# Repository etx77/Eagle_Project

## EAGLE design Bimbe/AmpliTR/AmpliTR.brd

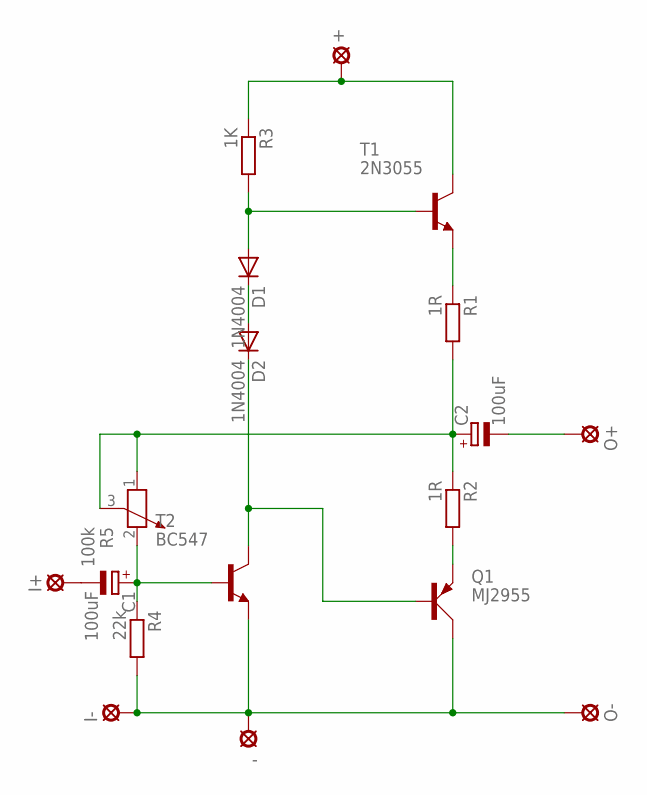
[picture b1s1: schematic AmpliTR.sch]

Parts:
+: LSP10
-: LSP10
C1, C2: 100uF; E2-5
D1, D2: 1N4004; DO41-10
I+: LSP10
I-: LSP10
O+: LSP10
O-: LSP10
Q1: MJ2955; TO3A
R1, R2: 1R; 0414V
R3: 1K; 0414V
R4: 22k; 0414V
R5: 100k; PT-10S
T1: 2N3055; TO3
T2: BC547; TO92

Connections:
unnamed: D1.C, D2.A
unnamed: D1.A, R3.2, T1.B
unnamed: +.MP, R3.1, T1.C, T1.C/ (C)
unnamed: R1.1, T1.E
unnamed: C2.+, R1.2, R2.1, R5.1, R5.3
unnamed: Q1.E, R2.2
unnamed: -.MP, I-.MP, O-.MP, Q1.C, Q1.C1 (C), R4.2, T2.1 (E)
unnamed: C1.+, R4.1, R5.2, T2.2 (B)
unnamed: D2.C, Q1.B, T2.3 (C)
unnamed: C2.-, O+.MP
unnamed: C1.-, I+.MP

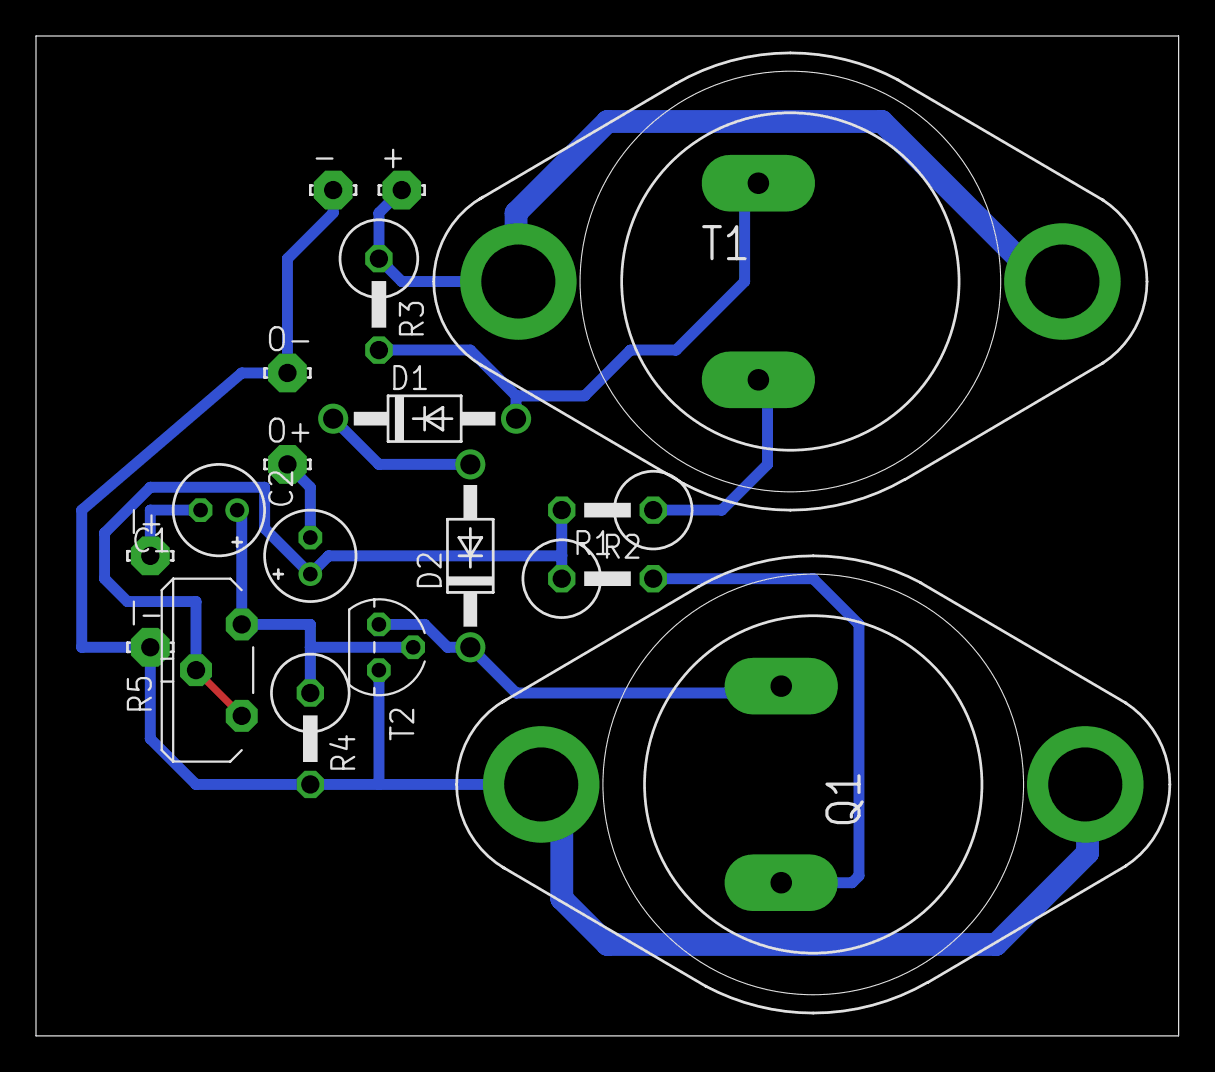
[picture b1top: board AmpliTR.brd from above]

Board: 2 copper layers, 63.5 x 55.5 mm, 18 parts (0 on the bottom side), 11 nets.

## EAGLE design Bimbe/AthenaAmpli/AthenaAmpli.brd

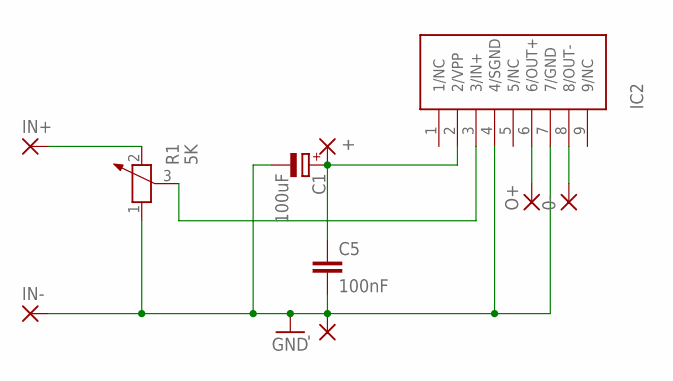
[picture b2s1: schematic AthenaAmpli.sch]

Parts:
0-: WIREPAD3,17/1,2; 3,17/1,2
+: WIREPAD3,17/1,2; 3,17/1,2
-: WIREPAD3,17/1,2; 3,17/1,2
C1: 100uF; E3,5-8
C5: 100nF; C050-024X044
IC2: TDA7056; SOT110-1
IN+: WIREPAD3,17/1,2; 3,17/1,2
IN-: WIREPAD3,17/1,2; 3,17/1,2
O+: WIREPAD3,17/1,2; 3,17/1,2
R1: 5K; PT-10S

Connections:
GND: -.1, C1.-, C5.2, IC2.4 (4/SGND), IC2.7 (7/GND), IN-.1, R1.1
unnamed: +.1, C1.+, C5.1, IC2.2 (2/VPP)
unnamed: IC2.3 (3/IN+), R1.3
unnamed: IN+.1, R1.2
unnamed: IC2.6 (6/OUT+), O+.1
unnamed: 0-.1, IC2.8 (8/OUT-)

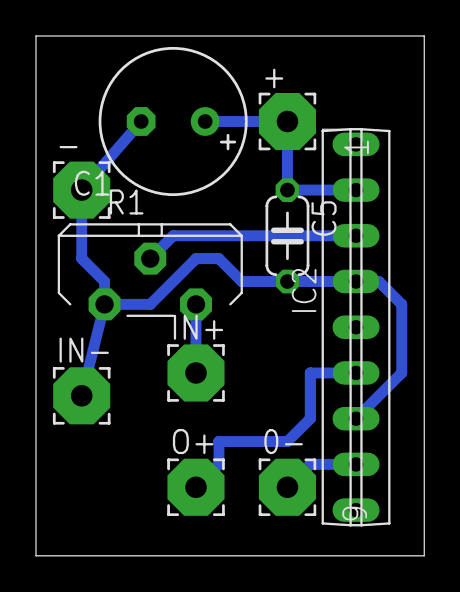
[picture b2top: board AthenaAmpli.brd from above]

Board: 2 copper layers, 21.6 x 28.9 mm, 10 parts (0 on the bottom side), 6 nets.

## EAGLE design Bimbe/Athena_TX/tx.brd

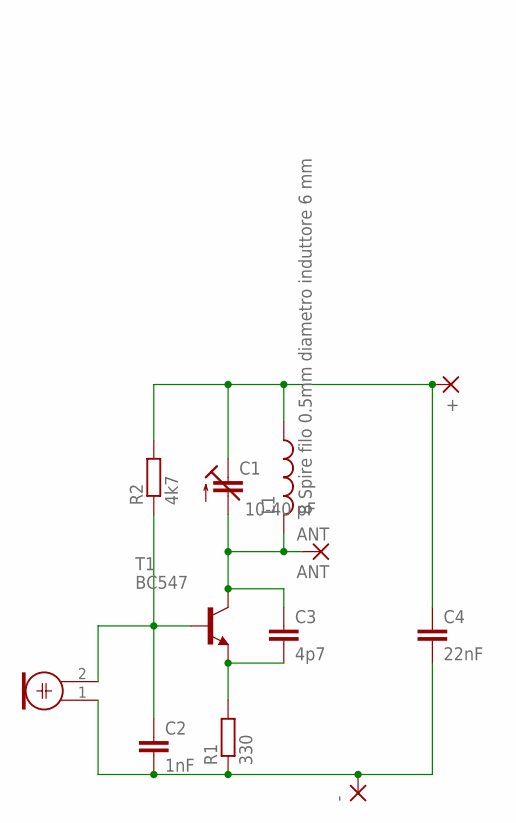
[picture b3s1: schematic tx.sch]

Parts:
+: 1,6/0,8
-: 1,6/0,8
ANT: ANT; 1,6/0,8
C1: 10-40 pF; 3008
C2: 1nF; C025-024X044
C3: 4p7; C025-024X044
C4: 22nF; C025-024X044
L1: 8 Spire filo 0.5mm diametro induttore 6 mm; 0207/10
M1: ELECTRET_MICROPHON-F6050AP; F6050AP
R1: 330; 0207/2V
R2: 4k7; 0207/2V
T1: BC547; TO92

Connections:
unnamed: +.1, C1.+ (E), C4.1, L1.1, R2.2
unnamed: C2.1, M1.2, R2.1, T1.2 (B)
unnamed: ANT.1, C1.- (A), C3.1, L1.2, T1.3 (C)
unnamed: -.1, C2.2, C4.2, M1.1, R1.1
unnamed: C3.2, R1.2, T1.1 (E)

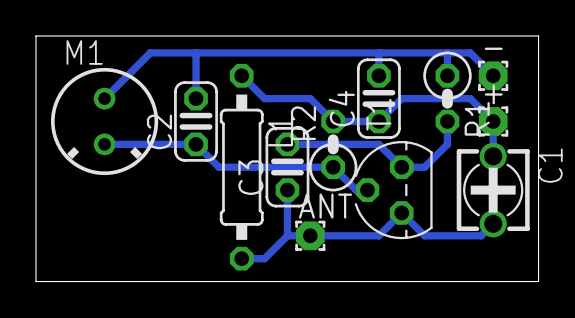
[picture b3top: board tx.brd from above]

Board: 2 copper layers, 27.9 x 13.6 mm, 12 parts (0 on the bottom side), 5 nets.

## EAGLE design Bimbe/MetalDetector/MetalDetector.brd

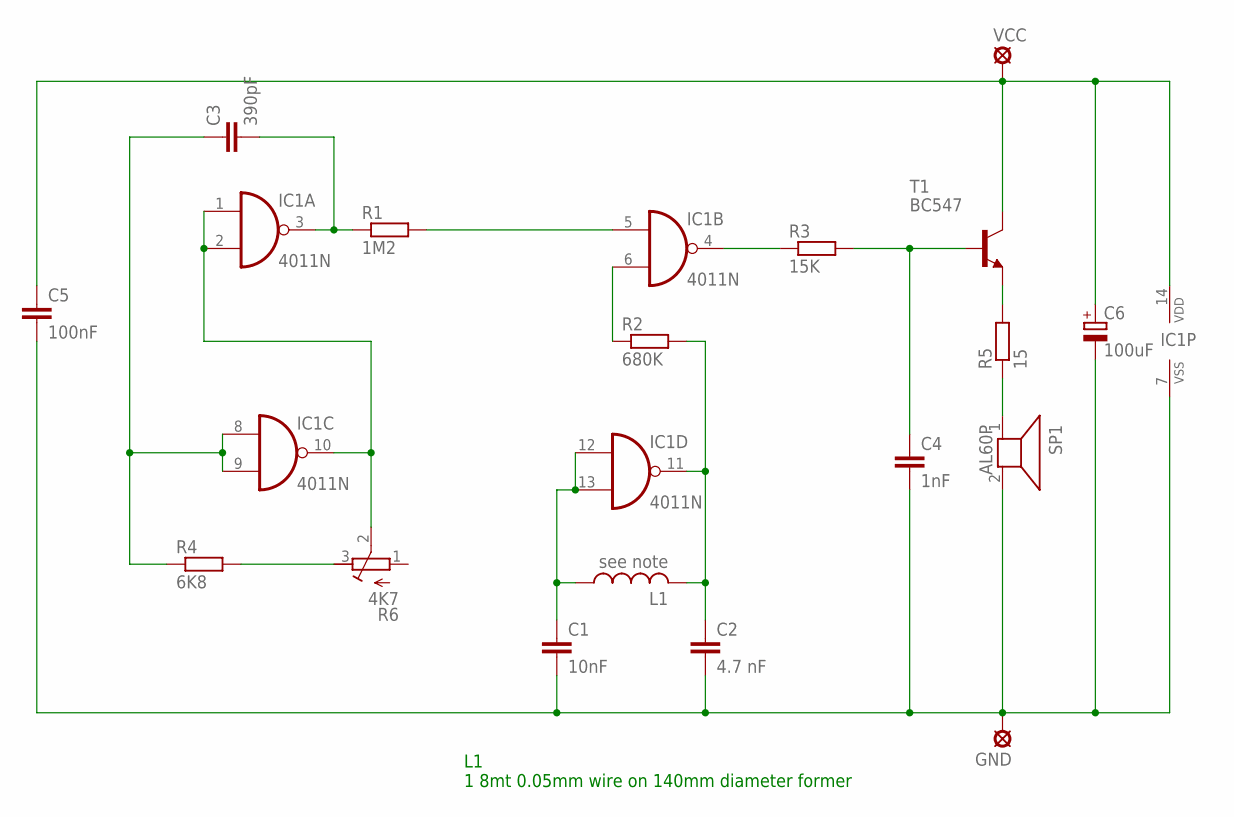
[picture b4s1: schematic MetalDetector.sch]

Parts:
C1: 10nF; C025-025X050
C2: 4.7 nF; C025-025X050
C3: 390pF; C025-025X050
C4: 1nF; C025-025X050
C5: 100nF; C025-025X050
C6: 100uF; E5-8,5
GND: LSP10
IC1: 4011N; DIL14
L1: see note; 6000-XXXX-RC
R1: 1M2; 0207/12
R2: 680K; 0207/12
R3: 15K; 0207/12
R4: 6K8; 0207/12
R5: 15; 0207/12
R6: 4K7; RTRIM3339P
SP1: AL60P
T1: BC547; TO92
VCC: LSP10

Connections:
unnamed: IC1.1 (I0), IC1.2 (I1), IC1.10 (O), R6.2 (S)
unnamed: C3.1, IC1.8 (I0), IC1.9 (I1), R4.1
unnamed: C1.1, IC1.12 (I0), IC1.13 (I1), L1.1
unnamed: C3.2, IC1.3 (O), R1.1
unnamed: IC1.5 (I0), R1.2
unnamed: R5.2, T1.1 (E)
unnamed: C2.1, IC1.11 (O), L1.2, R2.2
unnamed: IC1.4 (O), R3.1
unnamed: C4.1, R3.2, T1.2 (B)
unnamed: R5.1, SP1.1
unnamed: C1.2, C2.2, C4.2, C5.2, C6.-, GND.MP, IC1.7 (VSS), SP1.2
unnamed: C5.1, C6.+, IC1.14 (VDD), T1.3 (C), VCC.MP
unnamed: IC1.6 (I1), R2.1
unnamed: R4.2, R6.3 (E)

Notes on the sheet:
L1 1 8mt 0.05mm wire on 140mm diameter former

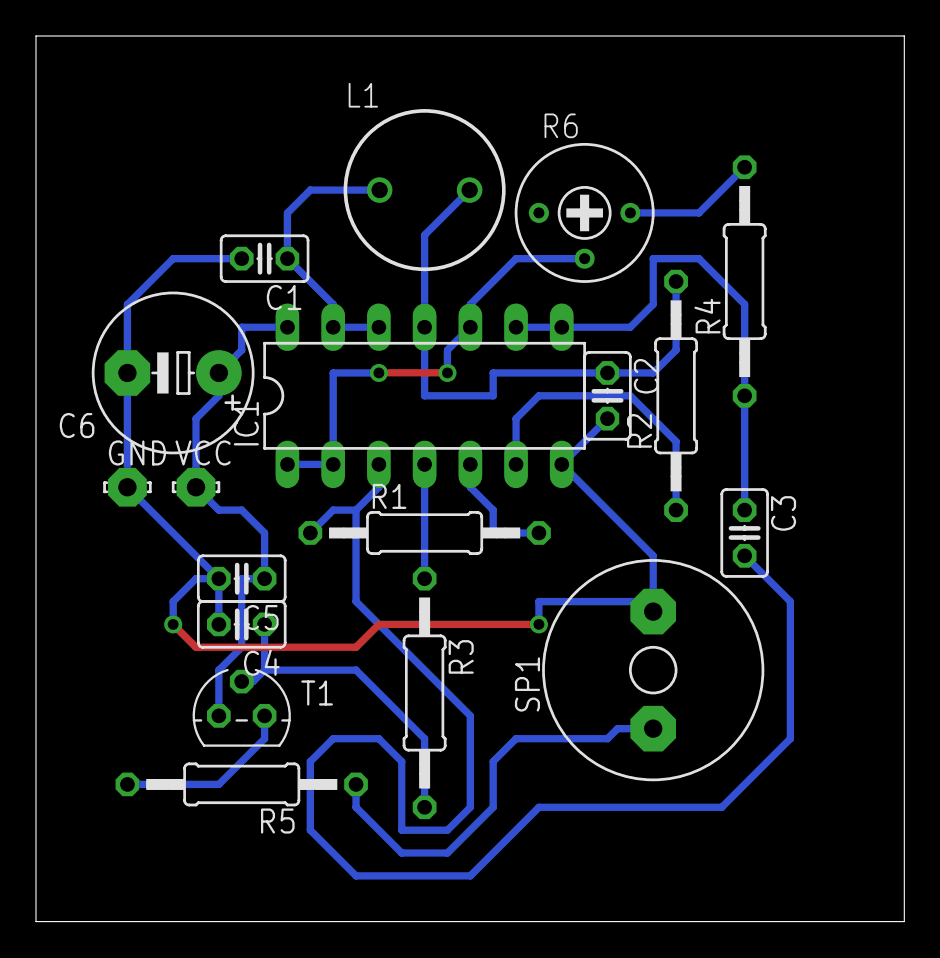
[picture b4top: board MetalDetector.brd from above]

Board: 2 copper layers, 48.2 x 49.2 mm, 18 parts (0 on the bottom side), 14 nets.

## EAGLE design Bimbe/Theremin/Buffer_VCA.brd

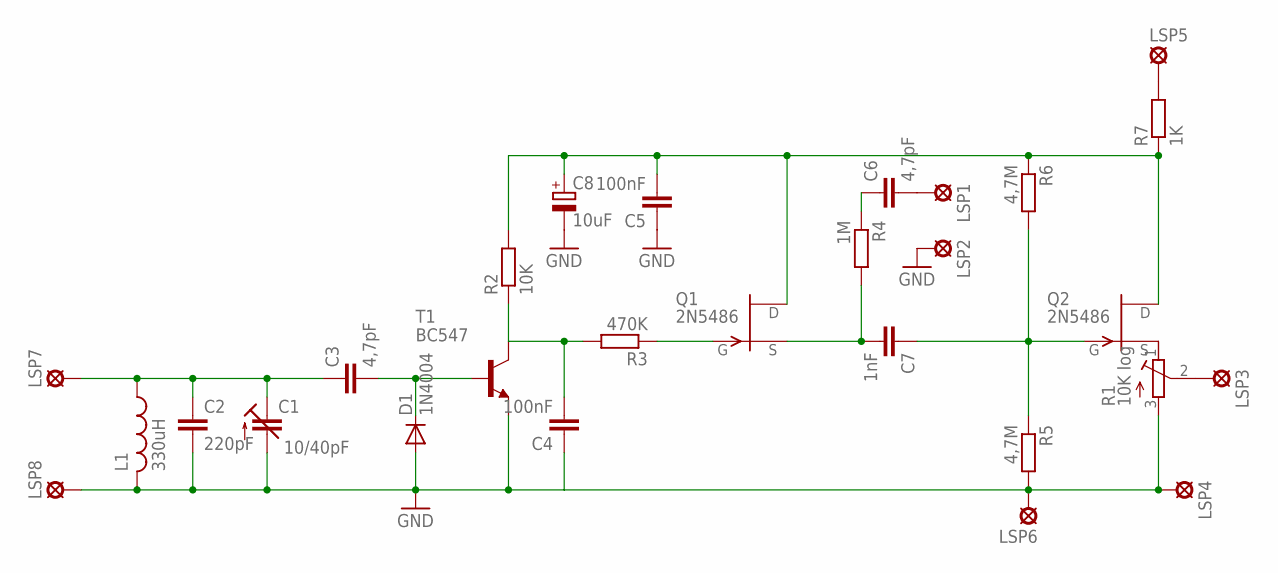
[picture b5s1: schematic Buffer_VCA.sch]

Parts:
C1: 10/40pF; CTRIM808-BC
C2: 220pF; C050-024X044
C3, C6: 4,7pF; C050-024X044
C4, C5: 100nF; C050-024X044
C7: 1nF; C050-024X044
C8: 10uF; E3,5-10
D1: 1N4004; DO41-10
L1: 330uH; 0204/7
LSP1, LSP2, LSP3, LSP4, LSP5, LSP6, LSP7, LSP8: LSP10
Q1, Q2: 2N5486; TO92-
R1: 10K log; RTRIMT93XB
R2: 10K; 0207/10
R3: 470K; 0207/10
R4: 1M; 0207/10
R5, R6: 4,7M; 0207/10
R7: 1K; 0207/10
T1: BC547; TO92

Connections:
unnamed: C1.1 (E), C2.1, C3.1, L1.1, LSP7.MP
unnamed: C6.2, LSP1.MP
unnamed: C3.2, D1.C, T1.2 (B)
unnamed: C4.2, R2.1, R3.2, T1.3 (C)
unnamed: C5.2, C8.+, Q1.3 (D), Q2.3 (D), R2.2, R6.1, R7.1
unnamed: Q1.1 (G), R3.1
unnamed: C6.1, R4.1
unnamed: C7.2, Q1.2 (S), R4.2
unnamed: C7.1, Q2.1 (G), R5.1, R6.2
unnamed: Q2.2 (S), R1.1 (E)
unnamed: LSP3.MP, R1.2 (S)
unnamed: LSP5.MP, R7.2
unnamed: C1.2 (A), C2.2, C4.1, C5.1, C8.-, D1.A, L1.2, LSP2.MP, LSP4.MP, LSP6.MP, LSP8.MP, R1.3 (A), R5.2, T1.1 (E)

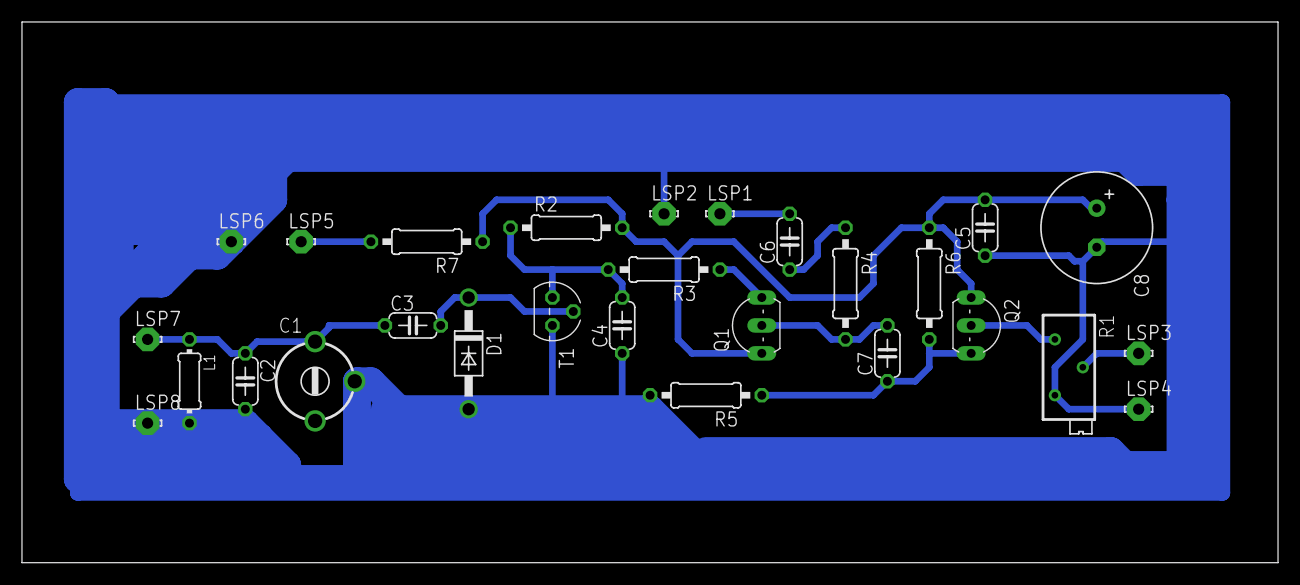
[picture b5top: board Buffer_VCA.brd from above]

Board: 2 copper layers, 114.3 x 49.2 mm, 28 parts (0 on the bottom side), 13 nets.

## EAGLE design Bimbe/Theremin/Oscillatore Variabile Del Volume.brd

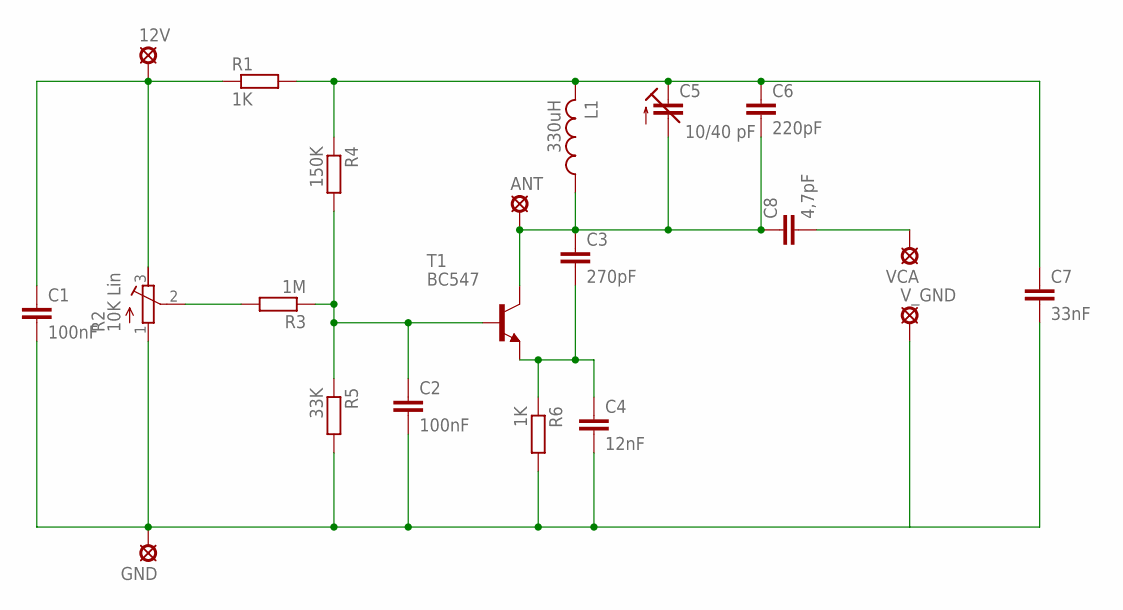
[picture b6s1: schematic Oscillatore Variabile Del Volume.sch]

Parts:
12V: LSP13
ANT: LSP10
C1, C2: 100nF; C7.5B3
C3: 270pF; C7.5B3
C4: 12nF; C7.5B3
C5: 10/40 pF; 3008
C6: 220pF; C7.5B3
C7: 33nF; C7.5B3
C8: 4,7pF; C2.5-5
GND: LSP13
L1: 330uH; 0204/7
R1, R6: 1K; 0207/10
R2: 10K Lin; RTRIM3339P
R3: 1M; 0207/10
R4: 150K; 0207/10
R5: 33K; 0207/10
T1: BC547; TO92
VCA: LSP13
V_GND: LSP13

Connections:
unnamed: 12V.MP, C1.1, R1.1, R2.3 (E)
unnamed: C5.+ (E), C6.1, C7.1, L1.2, R1.2, R4.1
unnamed: C2.1, R3.1, R4.2, R5.1, T1.2 (B)
unnamed: R2.2 (S), R3.2
unnamed: C3.2, C4.1, R6.1, T1.1 (E)
unnamed: C8.2, VCA.MP
unnamed: C1.2, C2.2, C4.2, C7.2, GND.MP, R2.1 (A), R5.2, R6.2, V_GND.MP
unnamed: ANT.MP, C3.1, C5.- (A), C6.2, C8.1, L1.1, T1.3 (C)

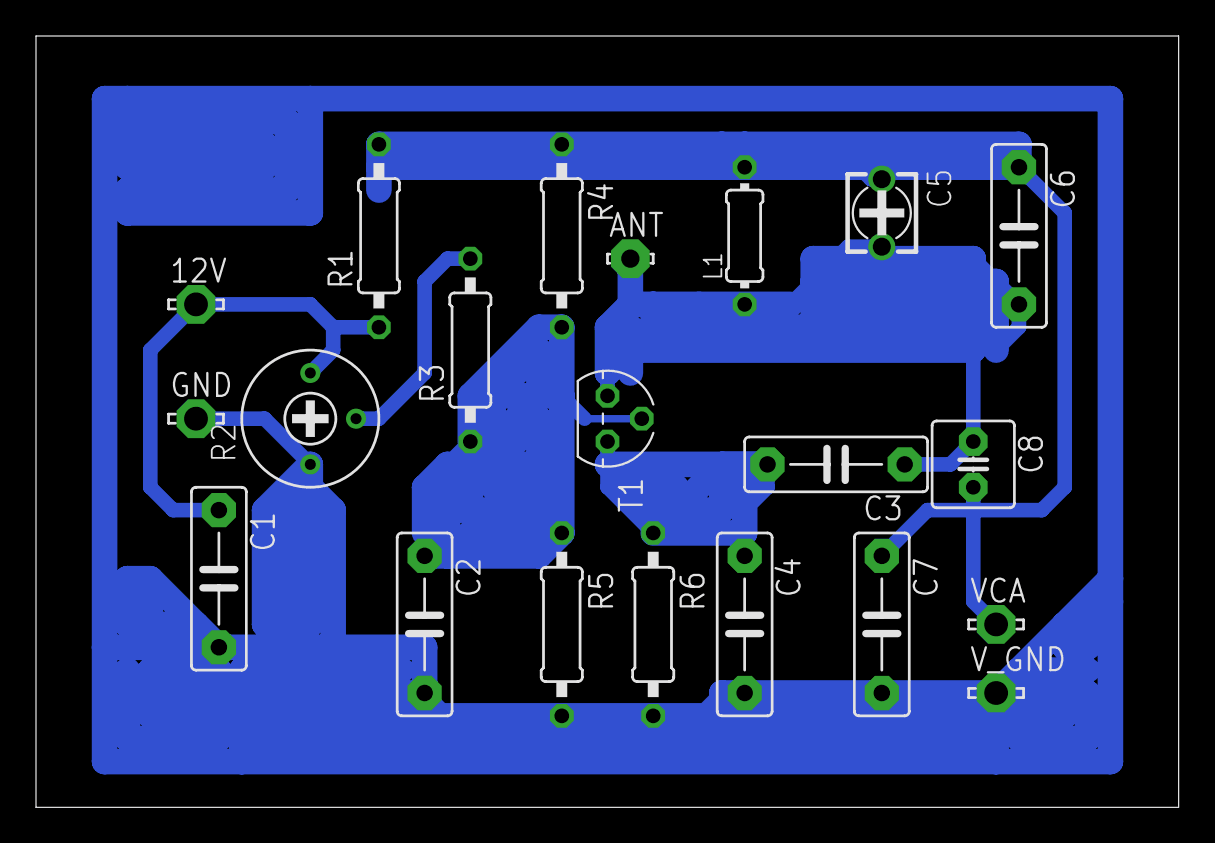
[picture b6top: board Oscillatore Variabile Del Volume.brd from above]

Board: 2 copper layers, 63.5 x 42.9 mm, 21 parts (0 on the bottom side), 8 nets.

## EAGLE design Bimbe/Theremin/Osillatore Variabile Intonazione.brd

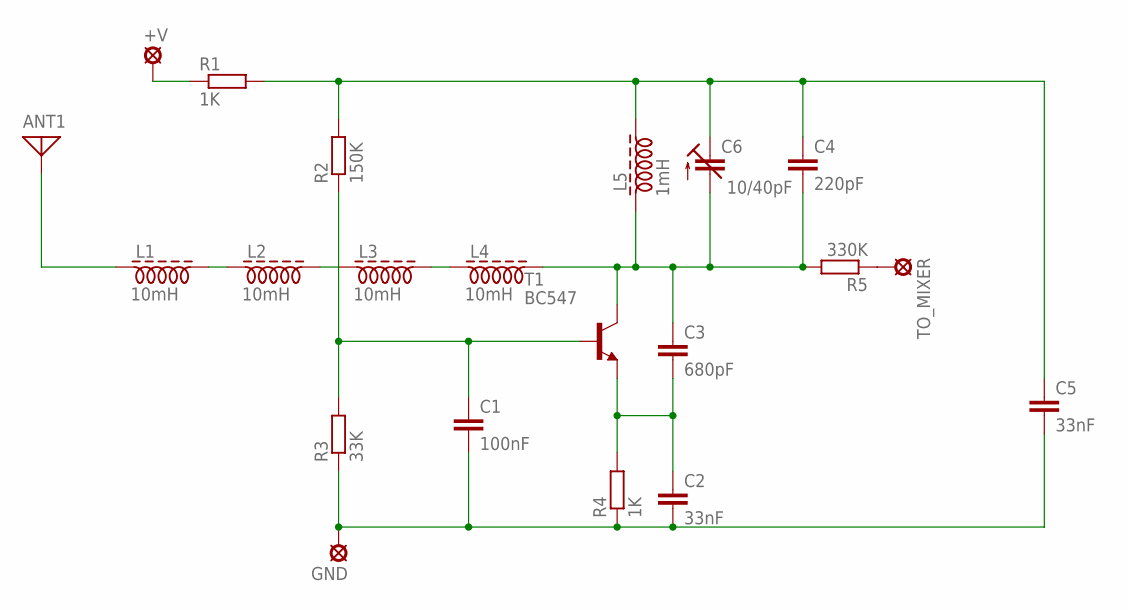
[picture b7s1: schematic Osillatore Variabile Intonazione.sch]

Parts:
+V: LSP10
ANT1: ANTENNA; PAD-01
C1: 100nF; C025-060X050
C2, C5: 33nF; C025-060X050
C3: 680pF; C025-060X050
C4: 220pF; C025-060X050
C6: 10/40pF; 3008
GND: LSP10
L1, L2, L3, L4: 10mH; Z28/7
L5: 1mH; Z28/7
R1, R4: 1K; 0207/7
R2: 150K; 0207/7
R3: 33K; 0207/7
R5: 330K; 0207/7
T1: BC547; TO92
TO_MIXER: LSP10

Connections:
unnamed: C4.1, C5.1, C6.+ (E), L5.2, R1.2, R2.2
unnamed: ANT1.1, L1.1
unnamed: L1.2, L2.1
unnamed: L2.2, L3.1
unnamed: L3.2, L4.1
unnamed: C3.1, C4.2, C6.- (A), L4.2, L5.1, R5.2, T1.3 (C)
unnamed: C1.1, R2.1, R3.2, T1.2 (B)
unnamed: +V.MP, R1.1
unnamed: C2.1, C3.2, R4.2, T1.1 (E)
unnamed: R5.1, TO_MIXER.MP
unnamed: C1.2, C2.2, C5.2, GND.MP, R3.1, R4.1

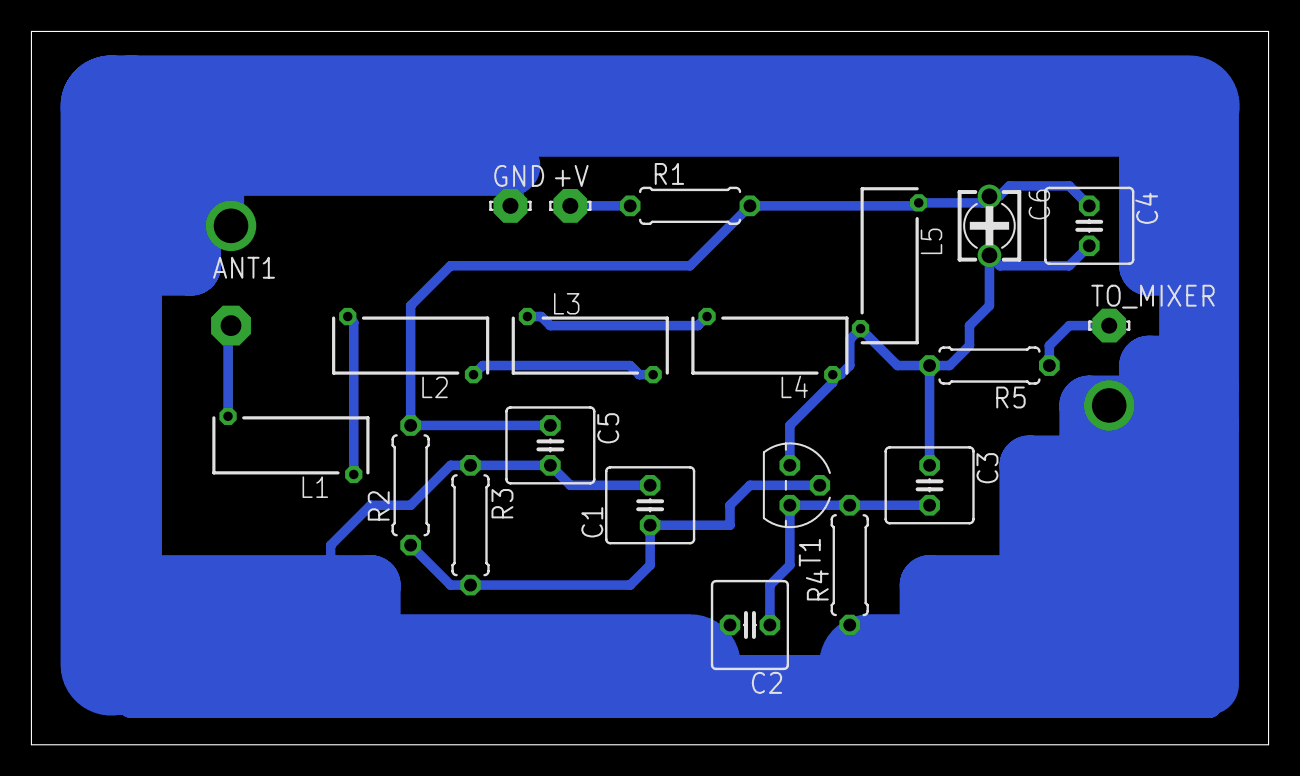
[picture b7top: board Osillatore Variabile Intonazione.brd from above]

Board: 2 copper layers, 78.7 x 45.4 mm, 21 parts (0 on the bottom side), 11 nets.

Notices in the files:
parts and their libraries:
SparkFun-Aesthetics: Licensing: Creative Commons ShareAlike 4.0 International - https://creativecommons.org/licenses/by-sa/4.0
